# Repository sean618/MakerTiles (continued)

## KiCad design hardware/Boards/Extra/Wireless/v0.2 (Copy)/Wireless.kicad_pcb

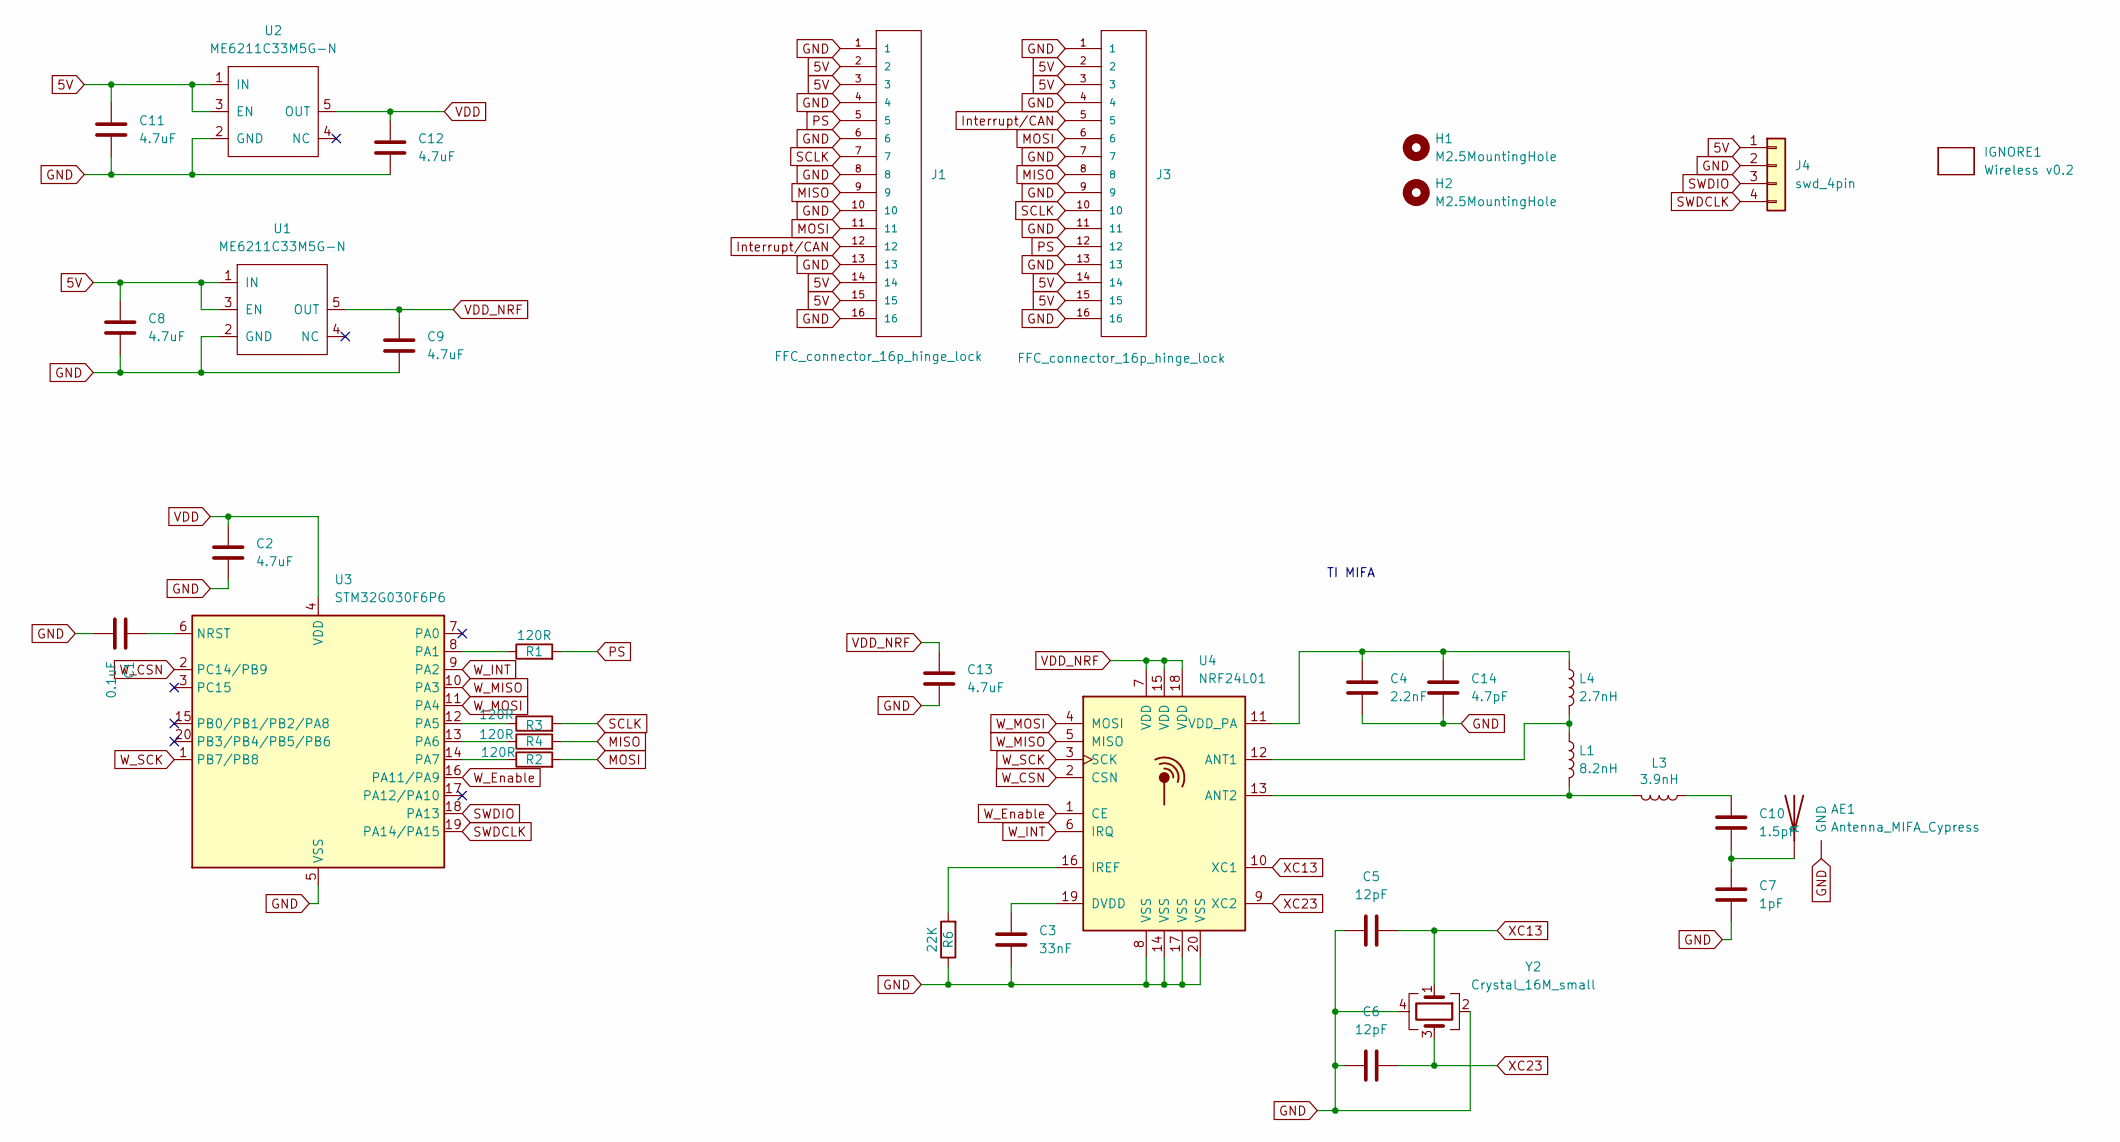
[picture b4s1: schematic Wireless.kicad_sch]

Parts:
AE1: Antenna_MIFA_Cypress; Antenna_cypress_MIFA
C1: 0.1uF; C_0402_1005Metric
C2, C8, C9, C11, C12, C13: 4.7uF; C_0402_1005Metric
C3: 33nF; C_0402_1005Metric
C4: 2.2nF; C_0402_1005Metric
C5, C6: 12pF; C_0402_1005Metric
C7: 1pF; C_0402_1005Metric
C10: 1.5pF; C_0402_1005Metric
C14: 4.7pF; C_0402_1005Metric
H1, H2: M2.5MountingHole; MountingHole_2.7mm_M2.5_ISO7380
IGNORE1: Wireless v0.2; BoardText
J1, J3: FFC_connector_16p_hinge_lock
J4: swd_4pin; swd_header
L1: 8.2nH; C_0402_1005Metric
L3: 3.9nH; C_0402_1005Metric
L4: 2.7nH; C_0402_1005Metric
R1, R2, R3, R4: 120R; R_0402_1005Metric
R6: 22K; R_0402_1005Metric
U1, U2: ME6211C33M5G-N; SOT-23-5
U3: STM32G030F6P6; TSSOP-20_4.4x6.5mm_P0.65mm
U4: NRF24L01; QFN-20-1EP_4x4mm_P0.5mm_EP2.5x2.5mm
Y2: Crystal_16M_small; Crystal_SMD_2016-4Pin_2.0x1.6mm

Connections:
5V: C8.1, C11.1, J1.2, J1.3, J1.14, J1.15, J3.2, J3.3, J3.14, J3.15, J4.1, U1.1 (IN), U1.3 (EN), U2.1 (IN), U2.3 (EN)
GND: AE1.2 (GND), C1.2, C2.2, C3.2, C4.2, C5.2, C6.2, C7.2, C8.2, C9.2, C11.2, C12.2, C13.2, C14.2, J1.1, J1.4, J1.6, J1.8, J1.10, J1.13, J1.16, J3.1, J3.4, J3.7, J3.9, J3.11, J3.13, J3.16, J4.2, R6.1, U1.2 (GND), U2.2 (GND), U3.5 (VSS), U4.8 (VSS), U4.14 (VSS), U4.17 (VSS), U4.20 (VSS), U4.21 (VSS), Y2.2 (GND), Y2.4 (GND)
MISO: J1.9, J3.8, R4.2
MOSI: J1.11, J3.6, R2.2
unnamed: AE1.1 (A), C7.1, C10.2
unnamed: C10.1, L3.1
unnamed: J1.12, J3.5
unnamed: C1.1, U3.6 (NRST)
unnamed: R1.1, U3.8 (PA1)
unnamed: R3.1, U3.12 (PA5)
unnamed: R4.1, U3.13 (PA6)
unnamed: R2.1, U3.14 (PA7)
unnamed: L1.1, L4.2, U4.12 (ANT1)
unnamed: L1.2, L3.2, U4.13 (ANT2)
unnamed: C3.1, U4.19 (DVDD)
unnamed: R6.2, U4.16 (IREF)
unnamed: C4.1, C14.1, L4.1, U4.11 (VDD_PA)
PS: J1.5, J3.12, R1.2
SCLK: J1.7, J3.10, R3.2
SWDCLK: J4.4, U3.19 (PA14/PA15)
SWDIO: J4.3, U3.18 (PA13)
VDD: C2.1, C12.1, U2.5 (OUT), U3.4 (VDD)
VDD_NRF: C9.1, C13.1, U1.5 (OUT), U4.7 (VDD), U4.15 (VDD), U4.18 (VDD)
W_CSN: U3.2 (PC14/PB9), U4.2 (CSN)
W_Enable: U3.16 (PA11/PA9), U4.1 (CE)
W_INT: U3.9 (PA2), U4.6 (IRQ)
W_MISO: U3.10 (PA3), U4.5 (MISO)
W_MOSI: U3.11 (PA4), U4.4 (MOSI)
W_SCK: U3.1 (PB7/PB8), U4.3 (SCK)
XC13: C5.1, U4.10 (XC1), Y2.1
XC23: C6.1, U4.9 (XC2), Y2.3

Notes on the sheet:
TI MIFA

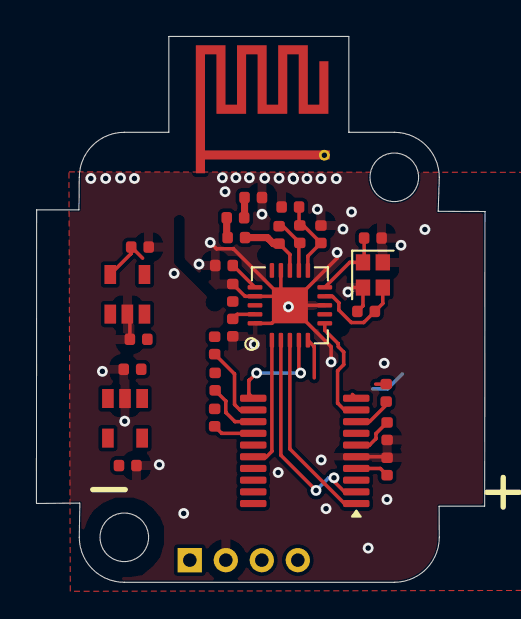
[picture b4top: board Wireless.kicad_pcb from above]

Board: 4 copper layers, 24.9 x 30.3 mm, 32 parts (0 on the bottom side), 26 nets.
